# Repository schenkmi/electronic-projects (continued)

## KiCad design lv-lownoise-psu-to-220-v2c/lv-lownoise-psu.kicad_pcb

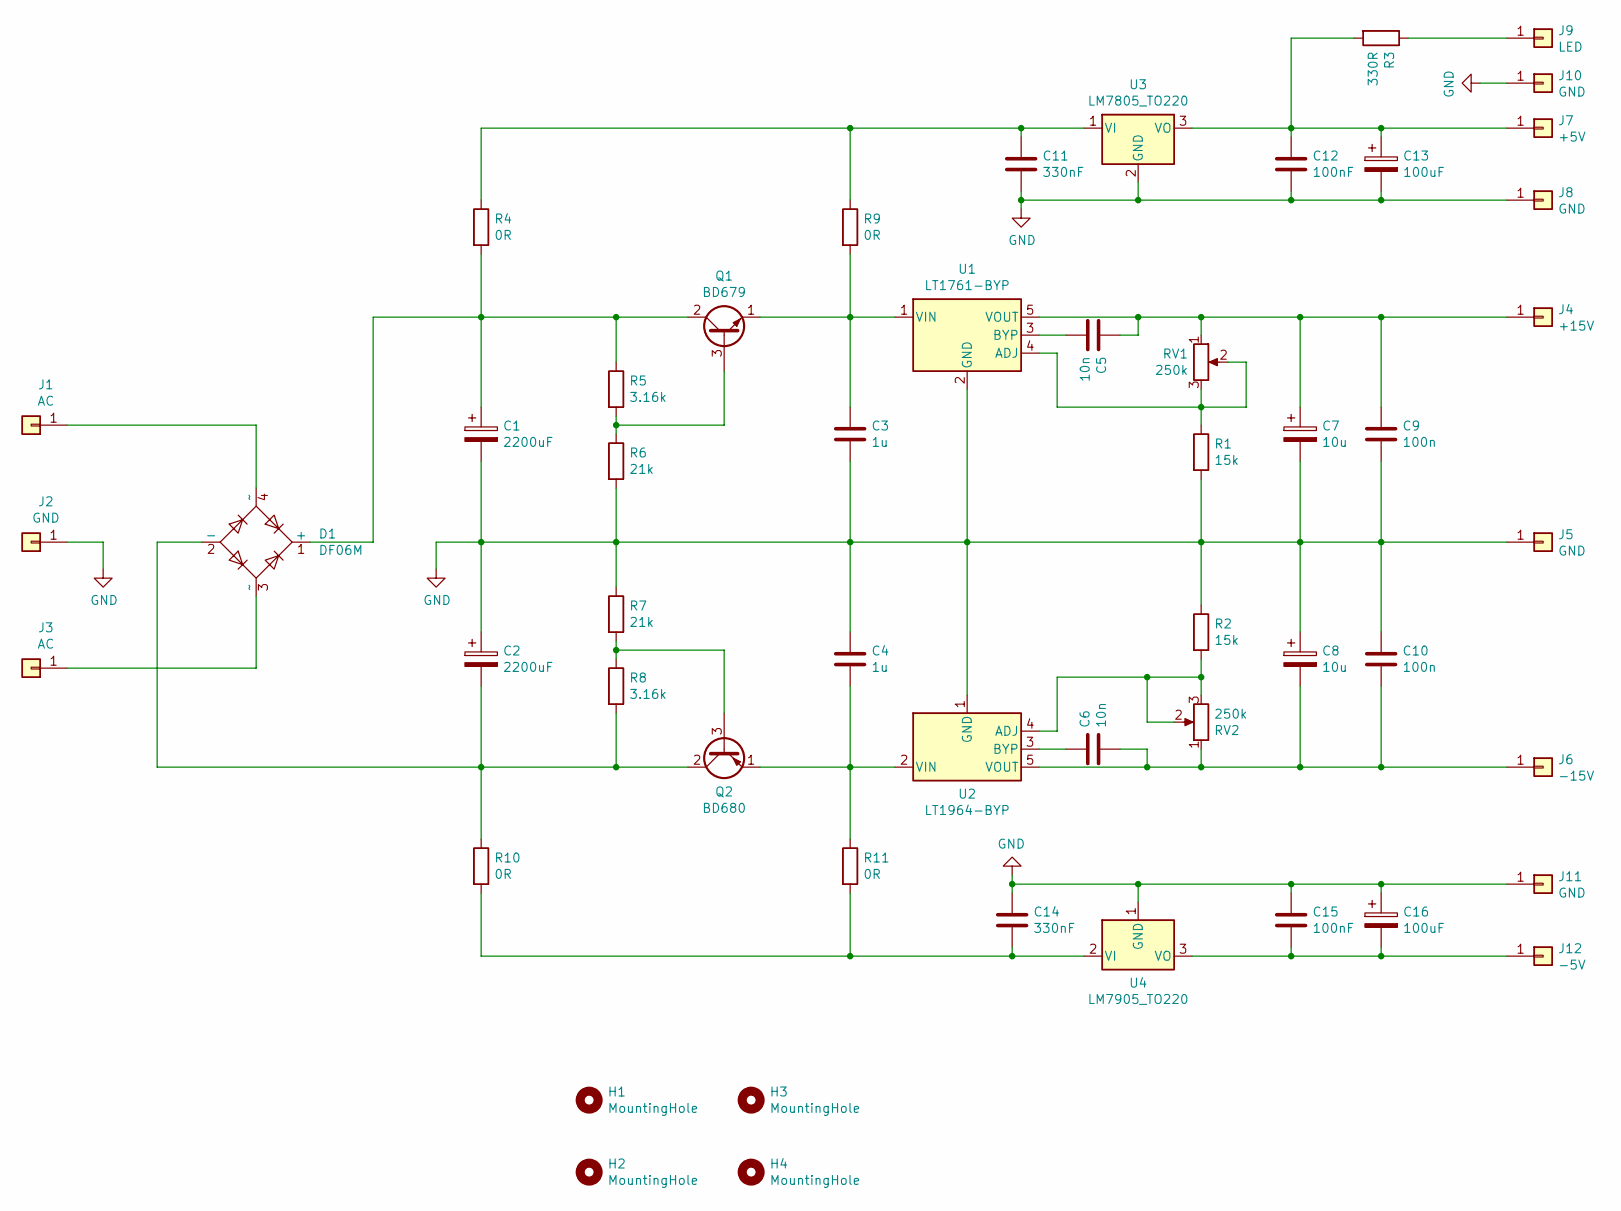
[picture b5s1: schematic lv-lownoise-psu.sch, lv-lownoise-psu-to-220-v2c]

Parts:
C1, C2: 2200uF; CP_Radial_D16.0mm_P7.50mm
C3, C4: 1u; C_0805_2012Metric_Pad1.18x1.45mm_HandSolder
C5, C6: 10n; C_0805_2012Metric_Pad1.18x1.45mm_HandSolder
C7, C8: 10u; CP_EIA-3528-12_Kemet-T_Pad1.50x2.35mm_HandSolder
C9, C10: 100n; C_0805_2012Metric_Pad1.18x1.45mm_HandSolder
C11, C14: 330nF; C_0805_2012Metric_Pad1.18x1.45mm_HandSolder
C12, C15: 100nF; C_0805_2012Metric_Pad1.18x1.45mm_HandSolder
C13, C16: 100uF; CP_Radial_D8.0mm_P3.50mm
D1: DF06M; Diode_Bridge_DIP-4_W7.62mm_P5.08mm
H1, H2, H3, H4: MountingHole; MountingHole_3.2mm_M3
J1, J3: AC; Pin_D1.3mm_L11.0mm
J2, J5, J8, J10, J11: GND; Pin_D1.3mm_L11.0mm
J4: +15V; Pin_D1.3mm_L11.0mm
J6: -15V; Pin_D1.3mm_L11.0mm
J7: +5V; Pin_D1.3mm_L11.0mm
J9: LED; Pin_D1.3mm_L11.0mm
J12: -5V; Pin_D1.3mm_L11.0mm
Q1: BD679; TO-126-3_Vertical
Q2: BD680; TO-126-3_Vertical
R1, R2: 15k; R_0805_2012Metric_Pad1.20x1.40mm_HandSolder
R3: 330R; R_0805_2012Metric_Pad1.20x1.40mm_HandSolder
R4, R9, R10, R11: 0R; R_0805_2012Metric_Pad1.15x1.40mm_HandSolder
R5, R8: 3.16k; R_0805_2012Metric_Pad1.20x1.40mm_HandSolder
R6, R7: 21k; R_0805_2012Metric_Pad1.20x1.40mm_HandSolder
RV1, RV2: 250k; Potentiometer_Bourns_3296W_Vertical
U1: LT1761-BYP; TSOT-23-5
U2: LT1964-BYP; TSOT-23-5
U3: LM7805_TO220; TO-220-3_Vertical
U4: LM7905_TO220; TO-220-3_Vertical

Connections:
GND: C1.2, C2.1, C3.2, C4.1, C7.2, C8.1, C9.2, C10.1, C11.2, C12.2, C13.2, C14.1, C15.1, C16.1, J2.1, J5.1, J8.1, J10.1, J11.1, R1.2, R2.1, R6.2, R7.1, U1.2 (GND), U2.1 (GND), U3.2 (GND), U4.1 (GND)
unnamed: C1.1, D1.1 (+), Q1.2 (C), R4.2, R5.1
unnamed: C2.2, D1.2 (-), Q2.2 (C), R8.2, R10.1
unnamed: C3.1, Q1.1 (E), R9.2, U1.1 (VIN)
unnamed: C4.2, Q2.1 (E), R11.1, U2.2 (VIN)
unnamed: C5.1, C7.1, C9.1, J4.1, RV1.1, U1.5 (VOUT)
unnamed: C5.2, U1.3 (BYP)
unnamed: C6.1, U2.3 (BYP)
unnamed: C6.2, C8.2, C10.2, J6.1, RV2.1, U2.5 (VOUT)
unnamed: C11.1, R4.1, R9.1, U3.1 (VI)
unnamed: C12.1, C13.1, J7.1, R3.2, U3.3 (VO)
unnamed: C14.2, R10.2, R11.2, U4.2 (VI)
unnamed: C15.2, C16.2, J12.1, U4.3 (VO)
unnamed: D1.3 (~~), J3.1
unnamed: D1.4 (~~), J1.1
unnamed: J9.1, R3.1
unnamed: Q1.3 (B), R5.2, R6.1
unnamed: Q2.3 (B), R7.2, R8.1
unnamed: R1.1, RV1.2, RV1.3, U1.4 (ADJ)
unnamed: R2.2, RV2.2, RV2.3, U2.4 (ADJ)

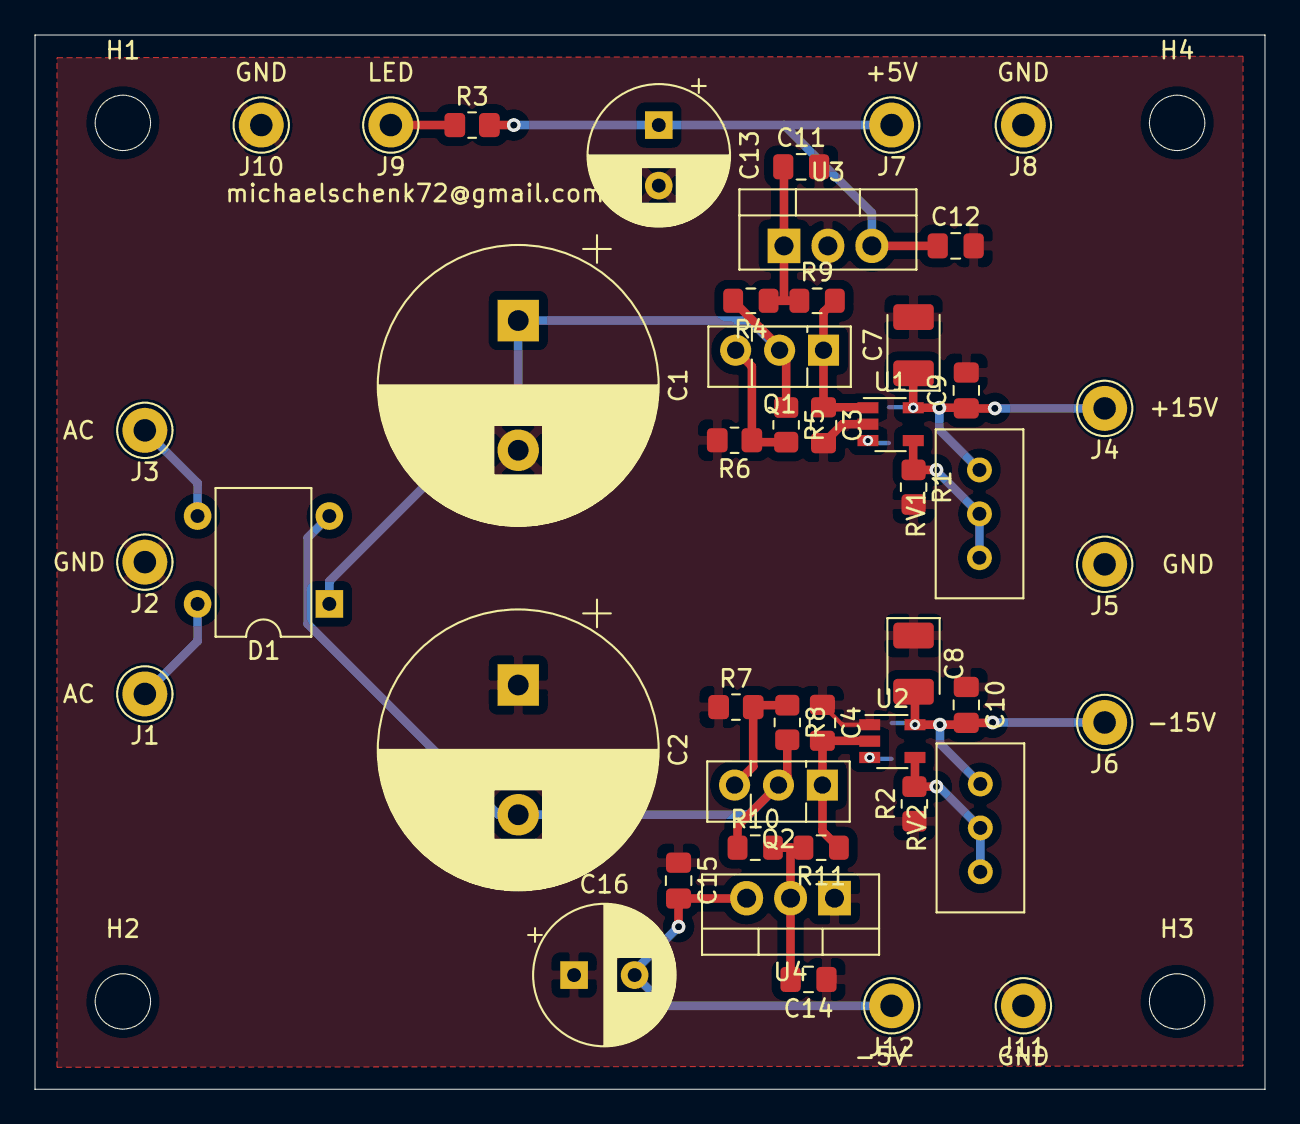
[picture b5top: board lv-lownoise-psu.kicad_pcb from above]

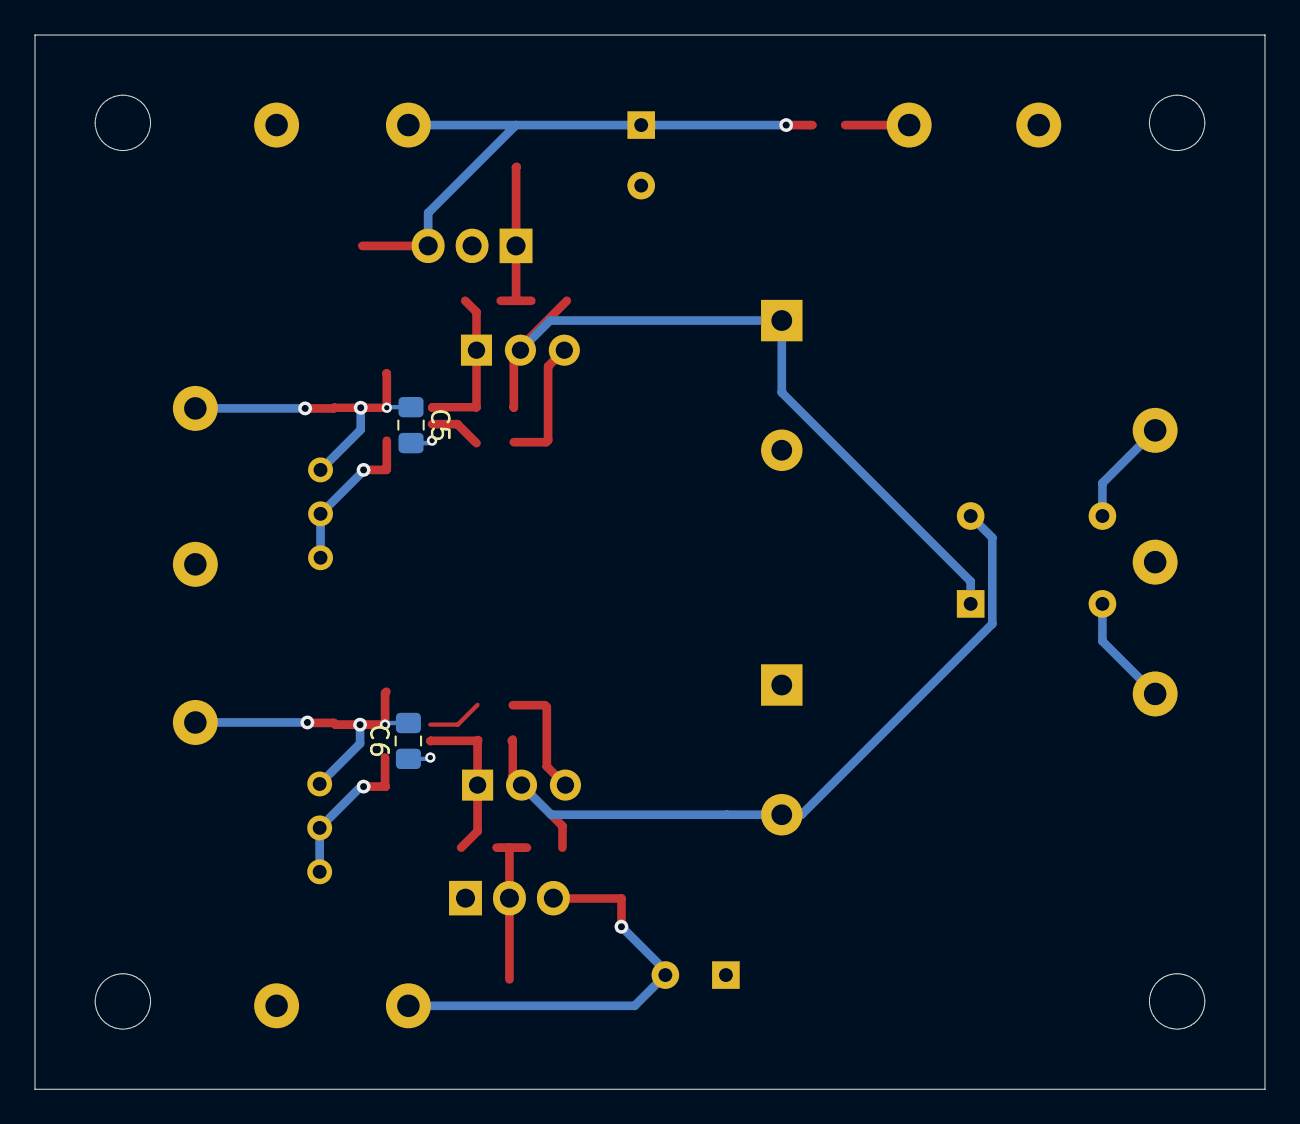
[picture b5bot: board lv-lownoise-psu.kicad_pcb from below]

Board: 2 copper layers, 71.1 x 61.0 mm, 52 parts (2 on the bottom side), 20 nets.
